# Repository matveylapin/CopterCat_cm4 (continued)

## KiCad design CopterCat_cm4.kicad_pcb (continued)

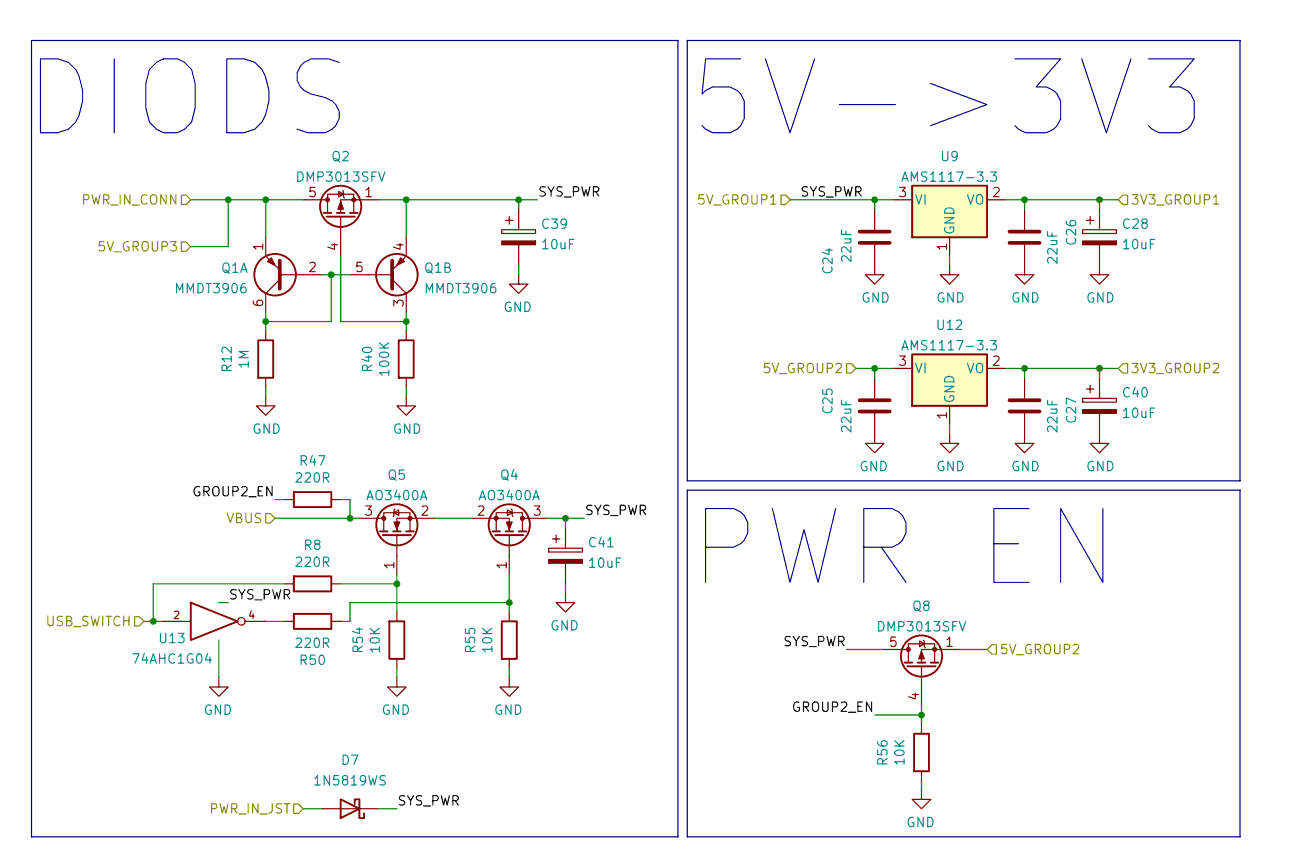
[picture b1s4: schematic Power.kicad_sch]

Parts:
C24, C25, C26, C27: 22uF; C_0402_1005Metric
C28, C39, C40, C41: 10uF; CP_EIA-3216-18_Kemet-A; Manufacturer_Part_Number CL31A226KAHNNNE
D7: 1N5819WS; D_SOD-323; Manufacturer_Part_Number 1N5819WS
Q1: MMDT3906; SOT-363_SC-70-6; Manufacturer_Part_Number MMDT3906
Q2: DMP3013SFV; Diodes_PowerDI3333-8; Manufacturer_Part_Number DMP3013SFV
Q4, Q5: AO3400A; SOT-23; Manufacturer_Part_Number AO3400A
Q8: DMP3013SFV; Diodes_PowerDI3333-8
R8, R47, R50: 220R; R_0402_1005Metric
R12: 1M; R_0402_1005Metric
R40: 100K; R_0402_1005Metric
R54, R55, R56: 10K; R_0402_1005Metric
U9, U12: AMS1117-3.3; SOT-223-3_TabPin2; Manufacturer_Part_Number AMS1117-3.3
U13: 74AHC1G04; SOT-353_SC-70-5; Manufacturer_Part_Number U74AHC1G04G-AL5-R

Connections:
/Connectors/PWR_IN_CONN: Q1.1 (E1), Q2.5 (D); also elsewhere on the board
/Connectors/PWR_IN_JST: D7.2 (A); also elsewhere on the board
/ESP32/ESP_3V3: C27.1, C40.1, U12.2 (VO); also elsewhere on the board
/Power/3V3_GROUP1: C26.1, C28.1, U9.2 (VO); also elsewhere on the board
/Power/5V_GROUP2: C25.1, Q8.1 (S), Q8.2 (S), Q8.3 (S), U12.3 (VI); also elsewhere on the board
/Power/GROUP2_EN: Q8.4 (G), R47.2, R56.1
/RPi_CM4/RPI_USB.ID: R8.2, U13.2; also elsewhere on the board
/STM32/STM_USB.VBUS: Q5.3 (D), R47.1; also elsewhere on the board
GND: C24.1, C25.2, C26.2, C27.2, C28.2, C39.2, C40.2, C41.2, R12.2, R40.2, R54.1, R55.2, R56.2, U9.1 (GND), U12.1 (GND), U13.3 (GND); also elsewhere on the board
unnamed: Q1.2 (B1), Q1.5 (B2), Q1.6 (C1), R12.1
unnamed: Q1.3 (C2), Q2.4 (G), R40.1
unnamed: Q4.1 (G), R50.2, R55.1
unnamed: Q4.2 (S), Q5.2 (S)
unnamed: Q5.1 (G), R8.1, R54.2
unnamed: R50.1, U13.4
VCC: C24.2, C39.1, C41.1, D7.1 (K), Q1.4 (E2), Q2.1 (S), Q2.2 (S), Q2.3 (S), Q4.3 (D), Q8.5 (D), U9.3 (VI), U13.5 (VCC); also elsewhere on the board

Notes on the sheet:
DIODS
PWR EN
5V->3V3

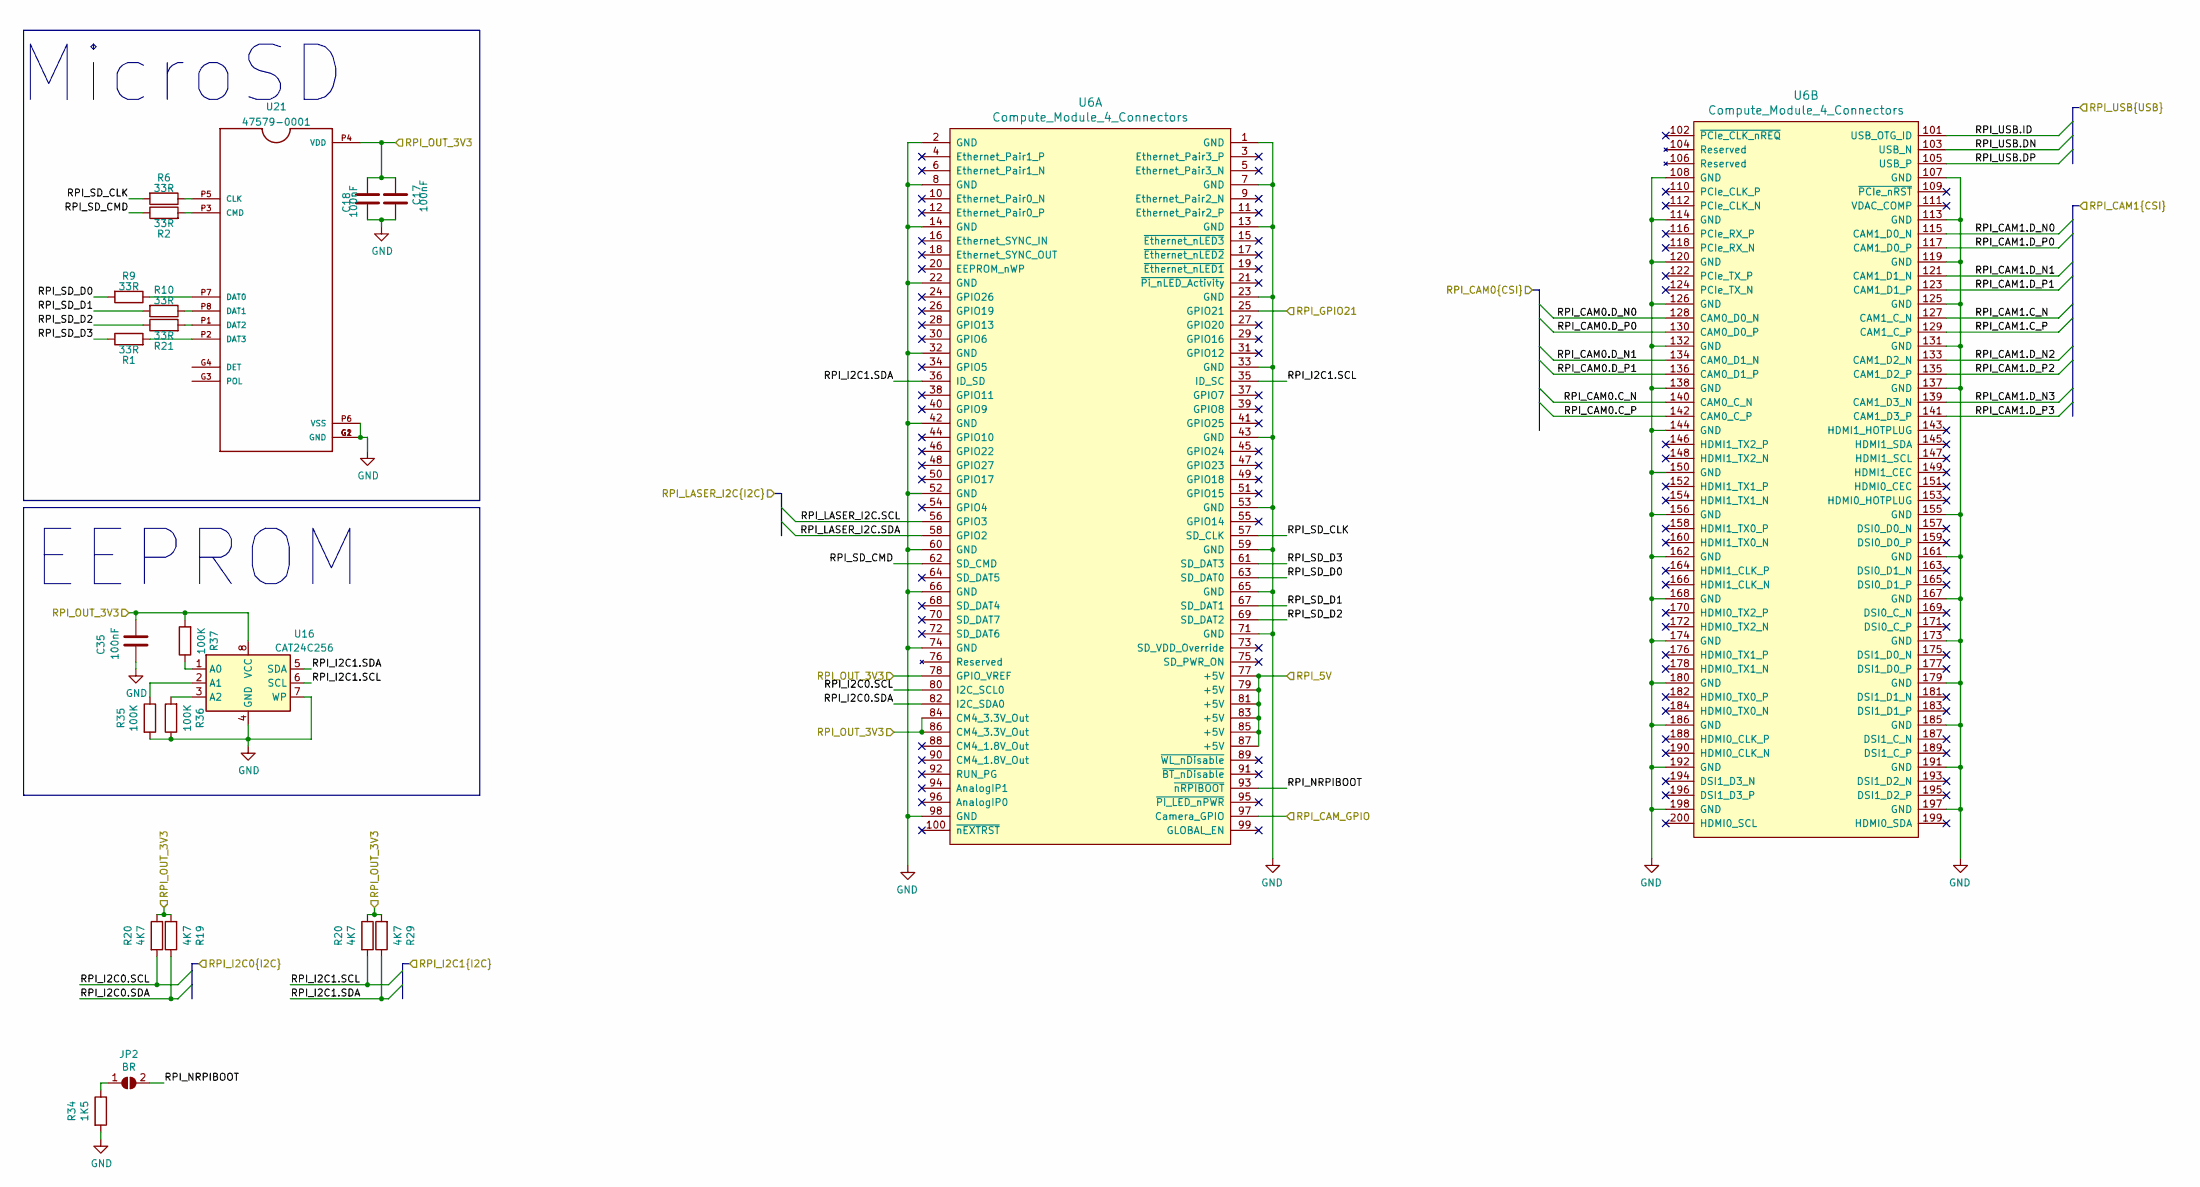
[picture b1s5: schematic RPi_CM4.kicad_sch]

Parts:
C17, C18, C35: 100nF; C_0402_1005Metric
JP2: BR; SolderJumper-2_P1.3mm_Open_TrianglePad1.0x1.5mm
R1, R2, R6, R9, R10, R21: 33R; R_0402_1005Metric
R19, R29: 4K7; R_0402_1005Metric
R20: 4.7K; R_0402_1005Metric
R34: 1K5; R_0402_1005Metric
R35, R36, R37: 100K; R_0402_1005Metric
U6: Compute_Module_4_Connectors; Raspberry-Pi-4-Compute-Module; Manufacturer_Part_Number DF40HC(3.0)-100DS-0.4V
U16: CAT24C256; DFN-8-1EP_3x2mm_P0.5mm_EP1.3x1.5mm; Manufacturer_Part_Number CAT24C256HU4IGT3
U21: 47579-0001; POS-8; Manufacturer_Part_Number TF-021B-H265

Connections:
/Connectors/RPI_CAM0.C_N: U6.140 (CAM0_C_N); also elsewhere on the board
/Connectors/RPI_CAM0.C_P: U6.142 (CAM0_C_P); also elsewhere on the board
/Connectors/RPI_CAM0.D_N0: U6.128 (CAM0_D0_N); also elsewhere on the board
/Connectors/RPI_CAM0.D_N1: U6.134 (CAM0_D1_N); also elsewhere on the board
/Connectors/RPI_CAM0.D_P0: U6.130 (CAM0_D0_P); also elsewhere on the board
/Connectors/RPI_CAM0.D_P1: U6.136 (CAM0_D1_P); also elsewhere on the board
/Connectors/RPI_CAM1.C_N: U6.127 (CAM1_C_N); also elsewhere on the board
/Connectors/RPI_CAM1.C_P: U6.129 (CAM1_C_P); also elsewhere on the board
/Connectors/RPI_CAM1.D_N0: U6.115 (CAM1_D0_N); also elsewhere on the board
/Connectors/RPI_CAM1.D_N1: U6.121 (CAM1_D1_N); also elsewhere on the board
/Connectors/RPI_CAM1.D_N2: U6.133 (CAM1_D2_N); also elsewhere on the board
/Connectors/RPI_CAM1.D_N3: U6.139 (CAM1_D3_N); also elsewhere on the board
/Connectors/RPI_CAM1.D_P0: U6.117 (CAM1_D0_P); also elsewhere on the board
/Connectors/RPI_CAM1.D_P1: U6.123 (CAM1_D1_P); also elsewhere on the board
/Connectors/RPI_CAM1.D_P2: U6.135 (CAM1_D2_P); also elsewhere on the board
/Connectors/RPI_CAM1.D_P3: U6.141 (CAM1_D3_P); also elsewhere on the board
/Connectors/RPI_CAM_GPIO: U6.97 (Camera_GPIO); also elsewhere on the board
/Connectors/RPI_GPIO21: U6.25 (GPIO21); also elsewhere on the board
/Connectors/RPI_I2C0.SDA: R19.1, U6.82 (I2C_SDA0); also elsewhere on the board
/Connectors/RPI_I2C1.SDA: R29.1, U6.36 (ID_SD), U16.5 (SDA); also elsewhere on the board
/Connectors/RPI_LASER_I2C.SCL: U6.56 (GPIO3); also elsewhere on the board
/Connectors/RPI_LASER_I2C.SDA: U6.58 (GPIO2); also elsewhere on the board
/Connectors/RPI_OUT_3V3: C17.1, C18.2, C35.2, R19.2, R20.1, R29.2, R37.2, U6.78 (GPIO_VREF), U6.84 (CM4_3.3V_Out), U6.86 (CM4_3.3V_Out), U16.8 (VCC), U21.P4 (VDD); also elsewhere on the board
/Power/5V_GROUP2: U6.77 (+5V), U6.79 (+5V), U6.81 (+5V), U6.83 (+5V), U6.85 (+5V), U6.87 (+5V); also elsewhere on the board
/RPi_CM4/RPI_NRPIBOOT: JP2.2 (B), U6.93 (~nRPIBOOT)
/RPi_CM4/RPI_SD_CLK: R6.2, U6.57 (SD_CLK)
/RPi_CM4/RPI_SD_CMD: R2.1, U6.62 (SD_CMD)
/RPi_CM4/RPI_SD_D0: R9.2, U6.63 (SD_DAT0)
/RPi_CM4/RPI_SD_D1: R10.2, U6.67 (SD_DAT1)
/RPi_CM4/RPI_SD_D2: R21.1, U6.69 (SD_DAT2)
/RPi_CM4/RPI_SD_D3: R1.1, U6.61 (SD_DAT3)
/RPi_CM4/RPI_USB.DN: U6.103 (USB_N); also elsewhere on the board
/RPi_CM4/RPI_USB.DP: U6.105 (USB_P); also elsewhere on the board
/RPi_CM4/RPI_USB.ID: U6.101 (USB_OTG_ID); also elsewhere on the board
GND: C17.2, C18.1, C35.1, R34.2, R35.2, R36.1, U6.1 (GND), U6.2 (GND), U6.7 (GND), U6.8 (GND), U6.13 (GND), U6.14 (GND), U6.22 (GND), U6.23 (GND), U6.32 (GND), U6.33 (GND), U6.42 (GND), U6.43 (GND), U6.52 (GND), U6.53 (GND), U6.59 (GND), U6.60 (GND), U6.65 (GND), U6.66 (GND), U6.71 (GND), U6.74 (GND), U6.98 (GND), U6.107 (GND), U6.108 (GND), U6.113 (GND), U6.114 (GND), U6.119 (GND), U6.120 (GND), U6.125 (GND), U6.126 (GND), U6.131 (GND), U6.132 (GND), U6.137 (GND), U6.138 (GND), U6.144 (GND), U6.150 (GND), U6.155 (GND), U6.156 (GND), U6.161 (GND), U6.162 (GND), U6.167 (GND), U6.168 (GND), U6.173 (GND), U6.174 (GND), U6.179 (GND), U6.180 (GND), U6.185 (GND), U6.186 (GND), U6.191 (GND), U6.192 (GND), U6.197 (GND), U6.198 (GND), U16.4 (GND), U16.7 (WP), U21.G1 (GND), U21.G2 (GND), U21.P6 (VSS); also elsewhere on the board
unnamed: JP2.1 (A), R34.1
unnamed: R1.2, U21.P2 (DAT3)
unnamed: R2.2, U21.P3 (CMD)
unnamed: R6.1, U21.P5 (CLK)
unnamed: R9.1, U21.P7 (DAT0)
unnamed: R10.1, U21.P8 (DAT1)
unnamed: R21.2, U21.P1 (DAT2)
unnamed: R35.1, U16.2 (A1)
unnamed: R36.2, U16.3 (A2)
unnamed: R37.1, U16.1 (A0)

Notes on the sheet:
EEPROM
MicroSD

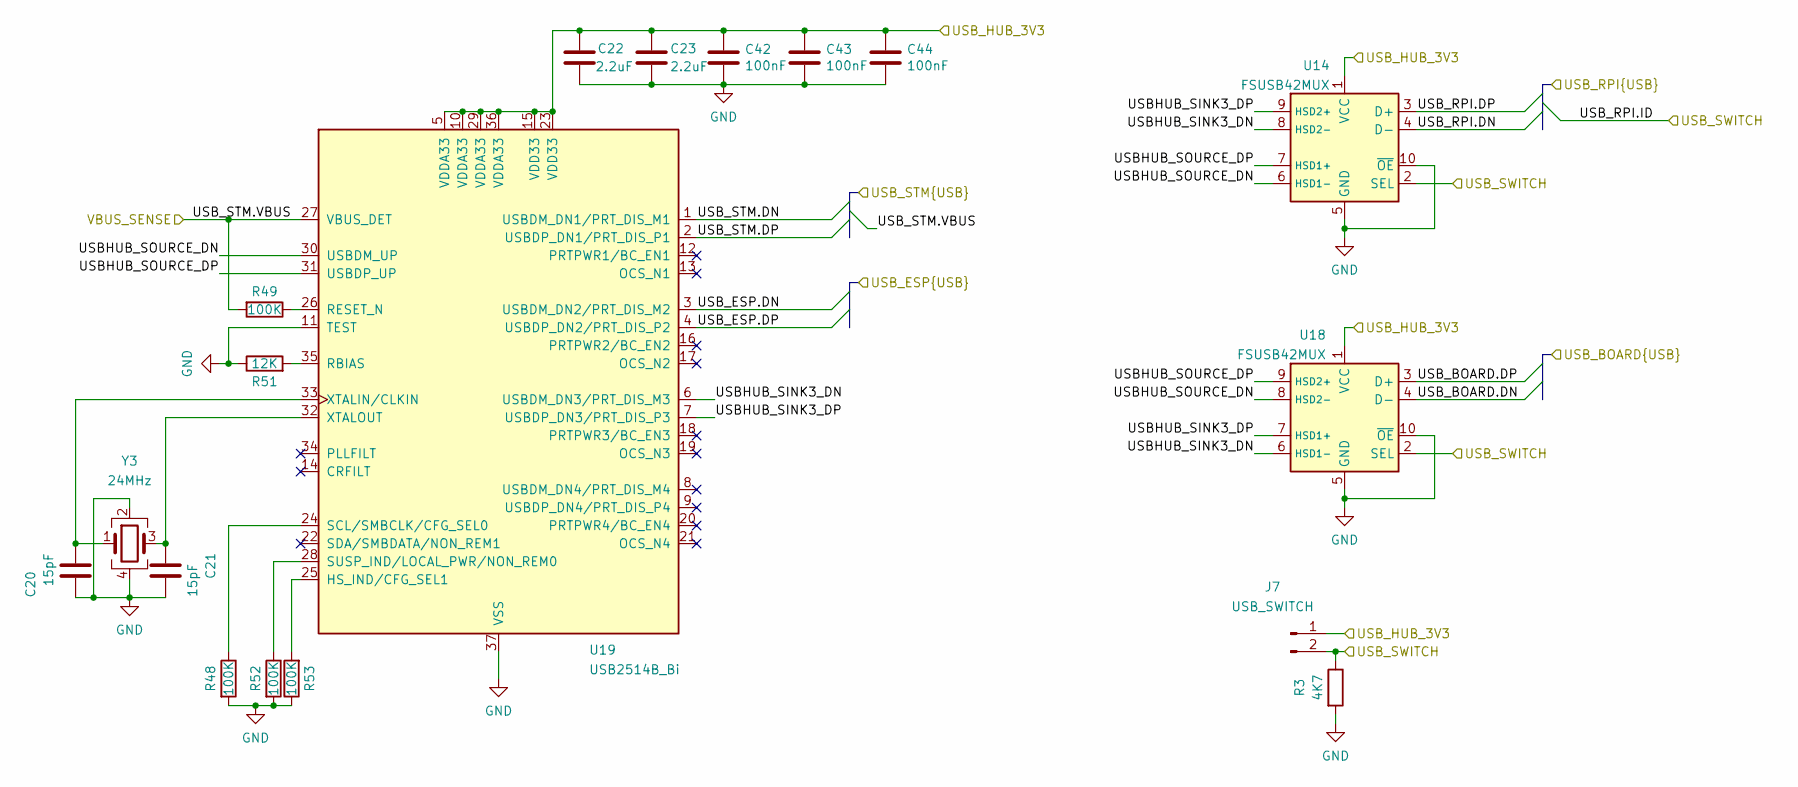
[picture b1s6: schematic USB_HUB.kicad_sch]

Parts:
C20, C21: 15pF; C_0402_1005Metric
C22, C23: 2.2uF; C_0402_1005Metric
C42, C43, C44: 100nF; C_0402_1005Metric
J7: USB_SWITCH; PinHeader_1x02_P2.54mm_Vertical
R3: 4K7; R_0402_1005Metric
R48, R49, R52, R53: 100K; R_0402_1005Metric
R51: 12K; R_0402_1005Metric
U14, U18: FSUSB42MUX; UQFN-10_1.4x1.8mm_P0.4mm; Manufacturer_Part_Number FSUSB42UMX
U19: USB2514B_Bi; QFN-36-1EP_6x6mm_P0.5mm_EP3.7x3.7mm; Manufacturer_Part_Number USB2514B-AEZC-TR
Y3: 24MHz; Crystal_SMD_2016-4Pin_2.0x1.6mm; Manufacturer_Part_Number OT201624MJBA4SL

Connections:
/Connectors/USB_BOARD.DN: U18.4 (D-); also elsewhere on the board
/Connectors/USB_BOARD.DP: U18.3 (D+); also elsewhere on the board
/ESP32/ESP_3V3: C22.2, C23.1, C42.1, C43.1, C44.1, J7.1, U14.1 (VCC), U18.1 (VCC), U19.5 (VDDA33), U19.10 (VDDA33), U19.15 (VDD33), U19.23 (VDD33), U19.29 (VDDA33), U19.36 (VDDA33); also elsewhere on the board
/ESP32/ESP_USB.DN: U19.3 (USBDM_DN2/PRT_DIS_M2); also elsewhere on the board
/ESP32/ESP_USB.DP: U19.4 (USBDP_DN2/PRT_DIS_P2); also elsewhere on the board
/RPi_CM4/RPI_USB.DN: U14.4 (D-); also elsewhere on the board
/RPi_CM4/RPI_USB.DP: U14.3 (D+); also elsewhere on the board
/RPi_CM4/RPI_USB.ID: J7.2, R3.1, U14.2 (SEL), U18.2 (SEL); also elsewhere on the board
/STM32/STM_USB.DN: U19.1 (USBDM_DN1/PRT_DIS_M1); also elsewhere on the board
/STM32/STM_USB.DP: U19.2 (USBDP_DN1/PRT_DIS_P1); also elsewhere on the board
/STM32/STM_USB.VBUS: R49.2, U19.27 (VBUS_DET); also elsewhere on the board
/USB_HUB/USBHUB_SINK3_DN: U14.8 (HSD2-), U18.6 (HSD1-), U19.6 (USBDM_DN3/PRT_DIS_M3)
/USB_HUB/USBHUB_SINK3_DP: U14.9 (HSD2+), U18.7 (HSD1+), U19.7 (USBDP_DN3/PRT_DIS_P3)
/USB_HUB/USBHUB_SOURCE_DN: U14.6 (HSD1-), U18.8 (HSD2-), U19.30 (USBDM_UP)
/USB_HUB/USBHUB_SOURCE_DP: U14.7 (HSD1+), U18.9 (HSD2+), U19.31 (USBDP_UP)
GND: C20.1, C21.2, C22.1, C23.2, C42.2, C43.2, C44.2, R3.2, R48.2, R51.1, R52.2, R53.1, U14.5 (GND), U14.10 (~OE), U18.5 (GND), U18.10 (~OE), U19.11 (TEST), U19.37 (VSS), Y3.2, Y3.4; also elsewhere on the board
unnamed: C20.2, U19.33 (XTALIN/CLKIN), Y3.1
unnamed: C21.1, U19.32 (XTALOUT), Y3.3
unnamed: R48.1, U19.24 (SCL/SMBCLK/CFG_SEL0)
unnamed: R49.1, U19.26 (RESET_N)
unnamed: R51.2, U19.35 (RBIAS)
unnamed: R52.1, U19.28 (SUSP_IND/LOCAL_PWR/NON_REM0)
unnamed: R53.2, U19.25 (HS_IND/CFG_SEL1)

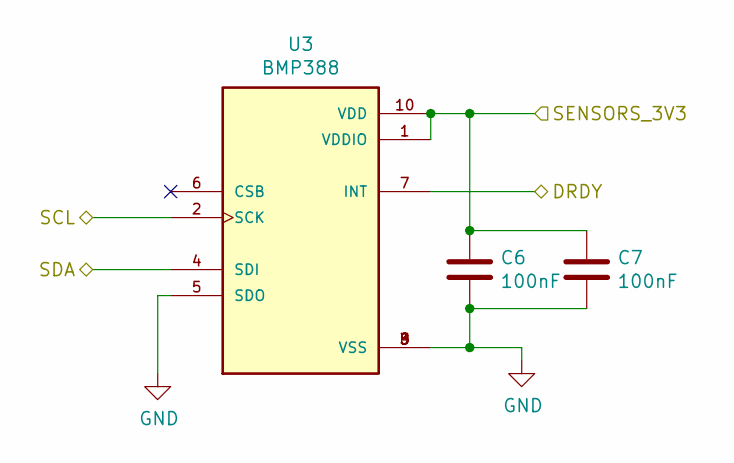
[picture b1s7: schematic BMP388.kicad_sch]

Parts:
C6, C7: 100nF; C_0402_1005Metric
U3: BMP388; PQFN50P200X200X80-10N; PARTREV 1.1

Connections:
/STM32/SENSORS_3V3: C6.1, C7.1, U3.1 (VDDIO), U3.10 (VDD); also elsewhere on the board
/STM32/STM_I2C4.DRDY1: U3.7 (INT); also elsewhere on the board
/STM32/STM_I2C4.SCL: U3.2 (SCK); also elsewhere on the board
/STM32/STM_I2C4.SDA: U3.4 (SDI); also elsewhere on the board
GND: C6.2, C7.2, U3.3 (VSS), U3.5 (SDO), U3.8 (VSS), U3.9 (VSS); also elsewhere on the board

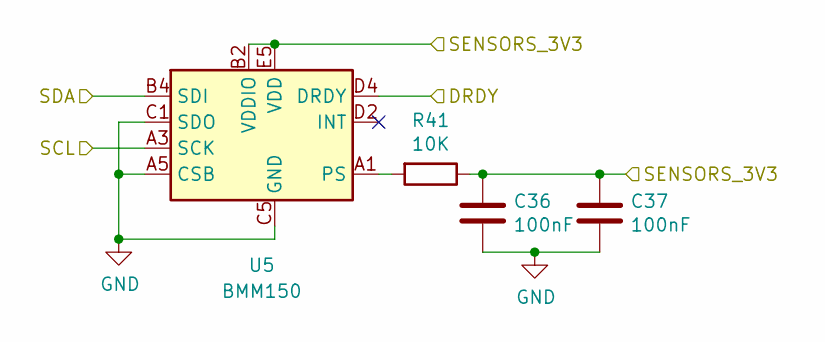
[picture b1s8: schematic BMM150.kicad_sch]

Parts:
C36, C37: 100nF; C_0402_1005Metric
R41: 10K; R_0402_1005Metric
U5: BMM150; WLCSP-12_1.56x1.56mm_P0.4mm; Manufacturer_Part_Number BMM150

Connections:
/STM32/SENSORS_3V3: C36.1, C37.1, R41.1, U5.B2 (VDDIO), U5.E5 (VDD); also elsewhere on the board
/STM32/STM_I2C4.DRDY2: U5.D4 (DRDY); also elsewhere on the board
/STM32/STM_I2C4.SCL: U5.A3 (SCK); also elsewhere on the board
/STM32/STM_I2C4.SDA: U5.B4 (SDI); also elsewhere on the board
GND: C36.2, C37.2, U5.A5 (CSB), U5.C1 (SDO), U5.C5 (GND), U5.E1 (GND), U5.E3 (GND); also elsewhere on the board
unnamed: R41.2, U5.A1 (PS)

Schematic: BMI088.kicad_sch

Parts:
C15, C16: 100nF; C_0402_1005Metric
U17: BMI088; PQFN50P450X300X100-16N; Manufacturer_Part_Number BMI088

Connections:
/STM32/SENSORS_3V3: C15.1, C16.1, U17.3 (VDD), U17.11 (VDDIO); also elsewhere on the board
/STM32/STM_SPI3.CS1: U17.14 (CSB1); also elsewhere on the board
/STM32/STM_SPI3.CS2: U17.5 (CSB2); also elsewhere on the board
/STM32/STM_SPI3.DRDY1: U17.16 (INT1); also elsewhere on the board
/STM32/STM_SPI3.DRDY2: U17.1 (INT2); also elsewhere on the board
/STM32/STM_SPI3.MISO: U17.10 (SDO2), U17.15 (SDO1); also elsewhere on the board
/STM32/STM_SPI3.MOSI: U17.9 (SDA/SDI); also elsewhere on the board
/STM32/STM_SPI3.SCK: U17.8 (SCL/SCK); also elsewhere on the board
GND: C15.2, C16.2, U17.2 (NC), U17.4 (GNDA), U17.6 (GNDIO), U17.7 (PS); also elsewhere on the board

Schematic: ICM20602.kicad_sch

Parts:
C3: 2.2uF; C_0402_1005Metric
C4, C5: 100nF; C_0402_1005Metric
U2: ICM-20602; LGA-16_3x3mm_P0.5mm_LayoutBorder3x5y; Manufacturer_Part_Number ICM-20602

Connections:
/STM32/SENSORS_3V3: C3.1, C5.1, U2.1 (VDDIO), U2.16 (VDD); also elsewhere on the board
/STM32/STM_SPI1.CS1: U2.5 (~CS); also elsewhere on the board
/STM32/STM_SPI1.DRDY1: U2.6 (INT); also elsewhere on the board
/STM32/STM_SPI1.MISO: U2.4 (SAO/SD0); also elsewhere on the board
/STM32/STM_SPI1.MOSI: U2.3 (SDA/SDI); also elsewhere on the board
/STM32/STM_SPI1.SCK: U2.2 (SCL/SPC); also elsewhere on the board
GND: C3.2, C4.2, C5.2, U2.8 (FSYNC), U2.9 (GND), U2.10 (GND), U2.11 (GND), U2.12 (GND), U2.13 (GND), U2.15 (GND); also elsewhere on the board
unnamed: C4.1, U2.14 (REGOUT)

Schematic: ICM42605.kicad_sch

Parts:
C13: 100nF; C_0402_1005Metric
C14: 2.2uF; C_0402_1005Metric
U7: ICM-42605; PQFN50P300X250X97-14N; PARTREV 0.4

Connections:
/STM32/SENSORS_3V3: C13.2, C14.1, U7.5 (VDDIO), U7.8 (VDD); also elsewhere on the board
/STM32/STM_SPI2.CS1: U7.12 (AP_CS); also elsewhere on the board
/STM32/STM_SPI2.DRDY2: U7.4 (INT1/INT); also elsewhere on the board
/STM32/STM_SPI2.MISO: U7.1 (AP_SDO/AP_ADO); also elsewhere on the board
/STM32/STM_SPI2.MOSI: U7.14 (AP_SDA/AP_SDIO/AP_SDI); also elsewhere on the board
/STM32/STM_SPI2.SCK: U7.13 (AP_SCL/AP_SCLK); also elsewhere on the board
GND: C13.1, C14.2, U7.2 (RESV_1), U7.3 (RESV_2), U7.6 (GND), U7.7 (RESV_3), U7.10 (RESV_4), U7.11 (RESV_5); also elsewhere on the board

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
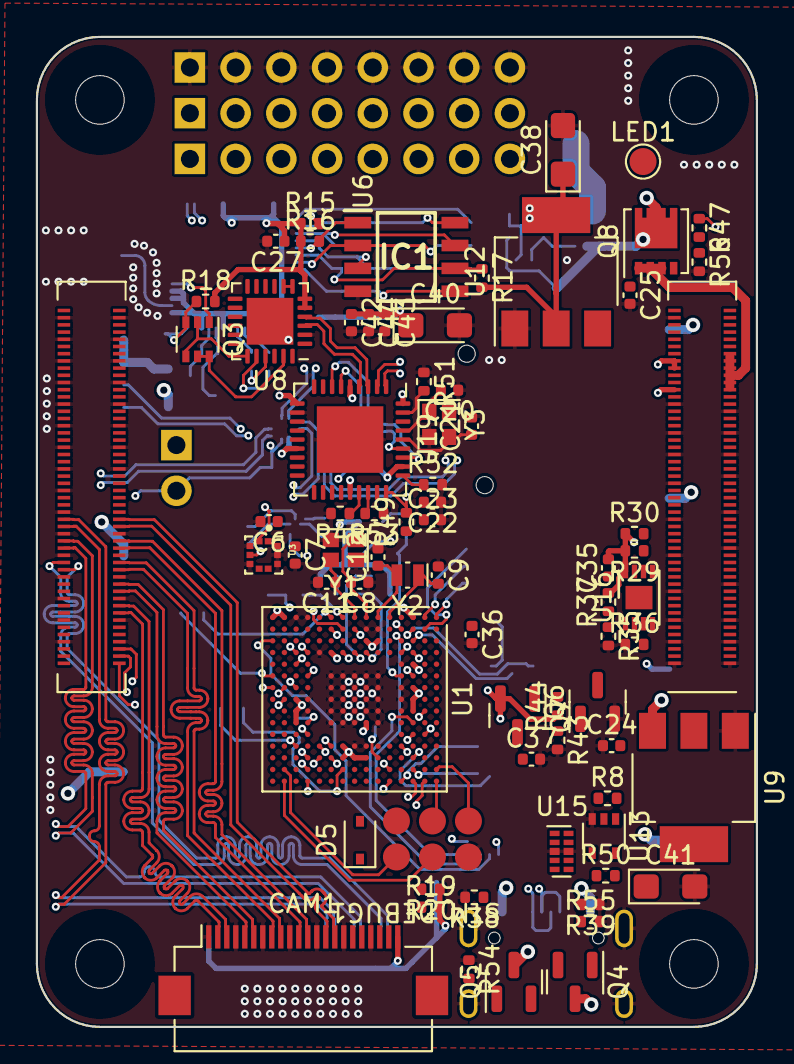
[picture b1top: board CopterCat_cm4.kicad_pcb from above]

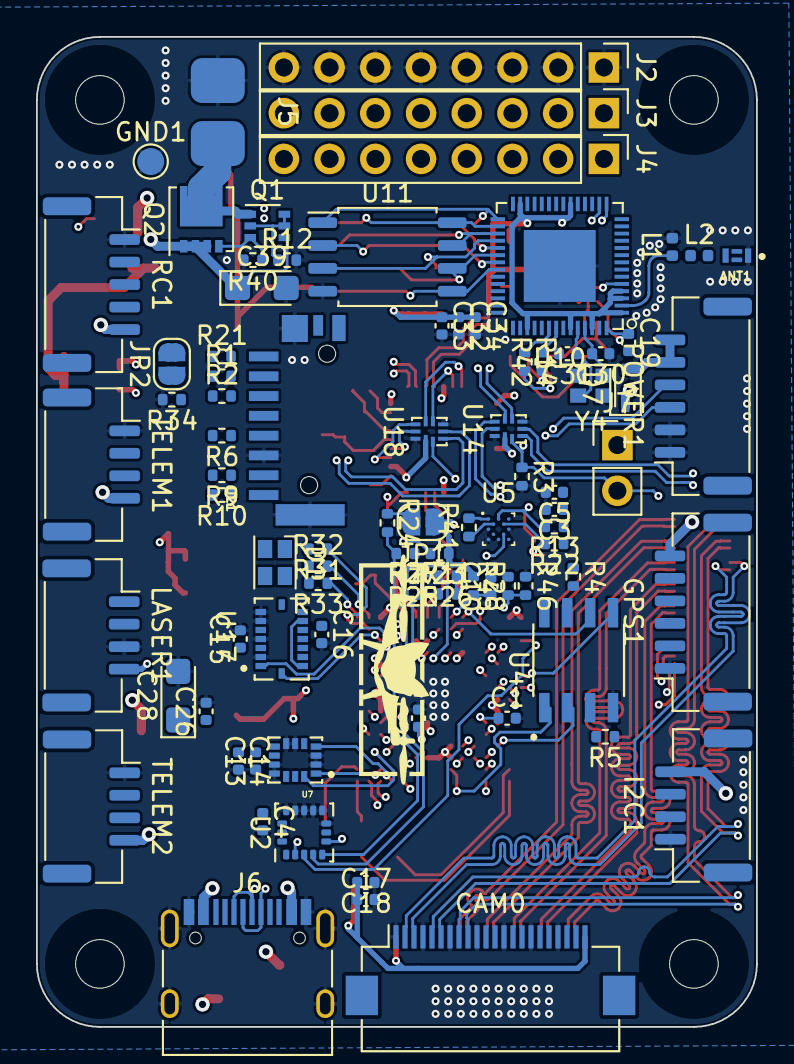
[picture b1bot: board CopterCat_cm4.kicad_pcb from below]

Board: 4 copper layers, 40.0 x 55.0 mm, 158 parts (86 on the bottom side), 180 nets.

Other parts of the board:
R20#2: 4.7K; R_0402_1005Metric

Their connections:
/Connectors/RPI_OUT_3V3: R20#2.1; also elsewhere on the board

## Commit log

2021-12-29 start adding usb-c
2021-12-30 working
2022-01-02 start migrating to kicad v6
2022-01-27 доработка схемы + делаем красиво
2022-02-03 плата практически готова
2022-02-03 продам гараж
2022-02-04 autoroute test
2022-02-05 тестирование
2022-02-05 second version
2022-02-06 первый релиз
2022-02-07 alfa
2022-02-07 Теперь точно релиз
2022-02-07 Adding esp32 gpio pins
2022-02-08 Little fix
2022-02-13 little fix 2
2022-02-13 забыл сохранить
2022-03-01 First order
2022-04-10 final
2022-04-23 аштфд
